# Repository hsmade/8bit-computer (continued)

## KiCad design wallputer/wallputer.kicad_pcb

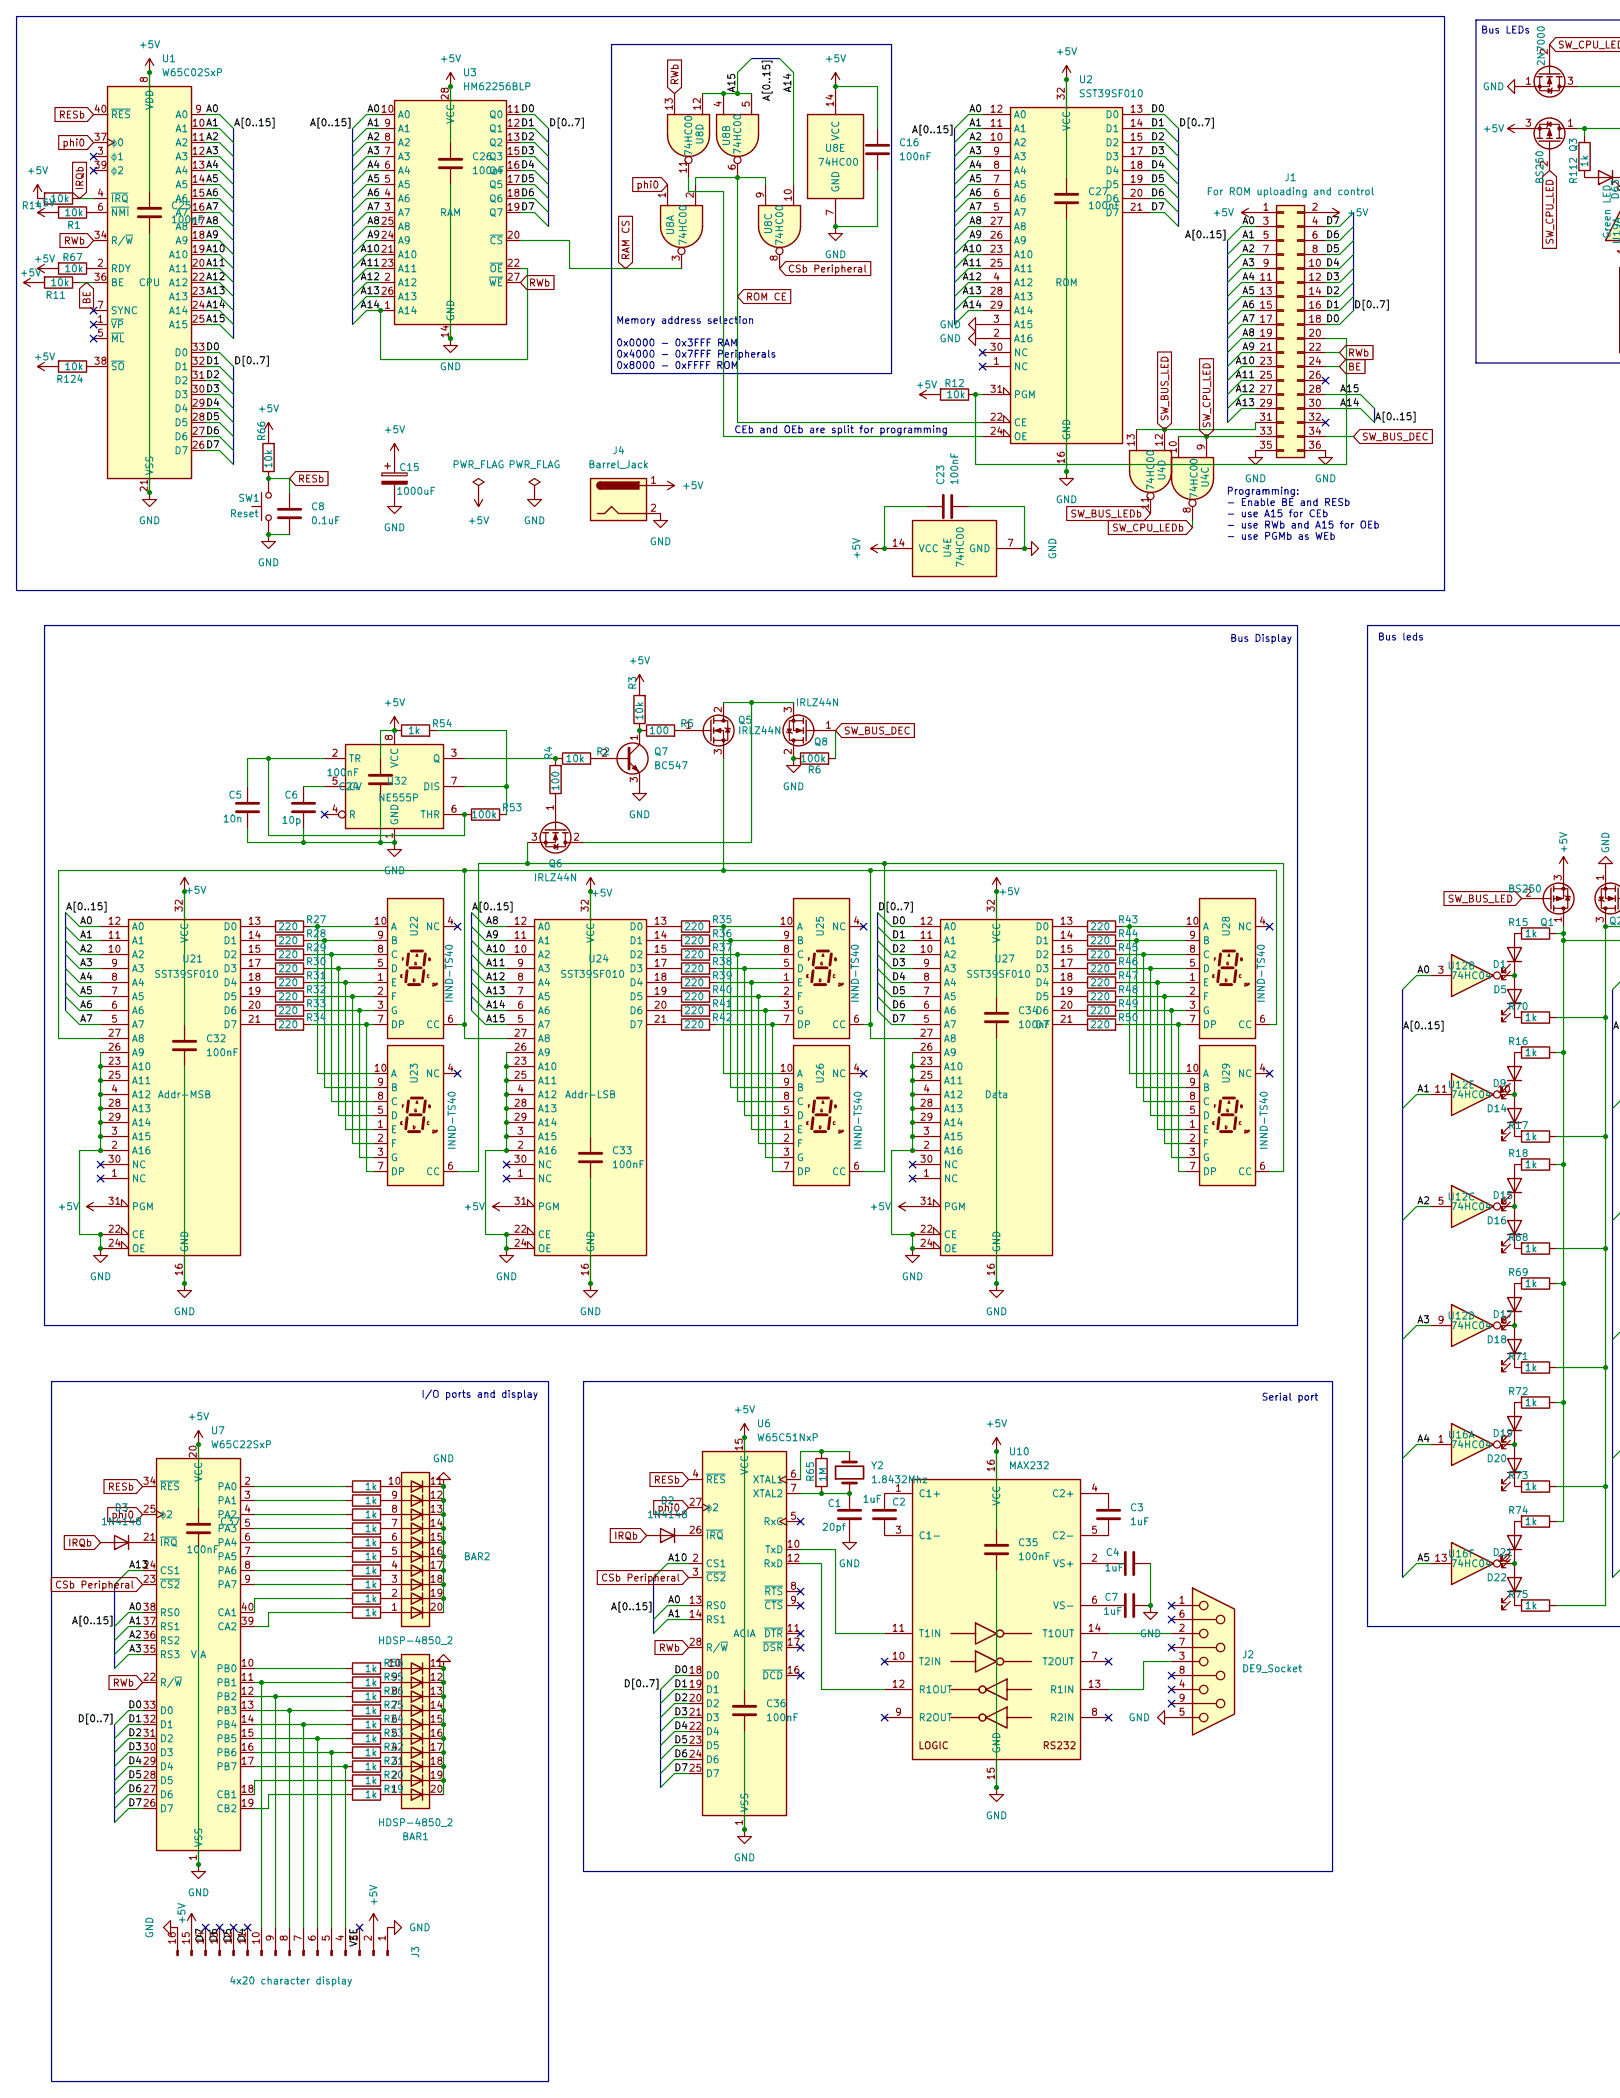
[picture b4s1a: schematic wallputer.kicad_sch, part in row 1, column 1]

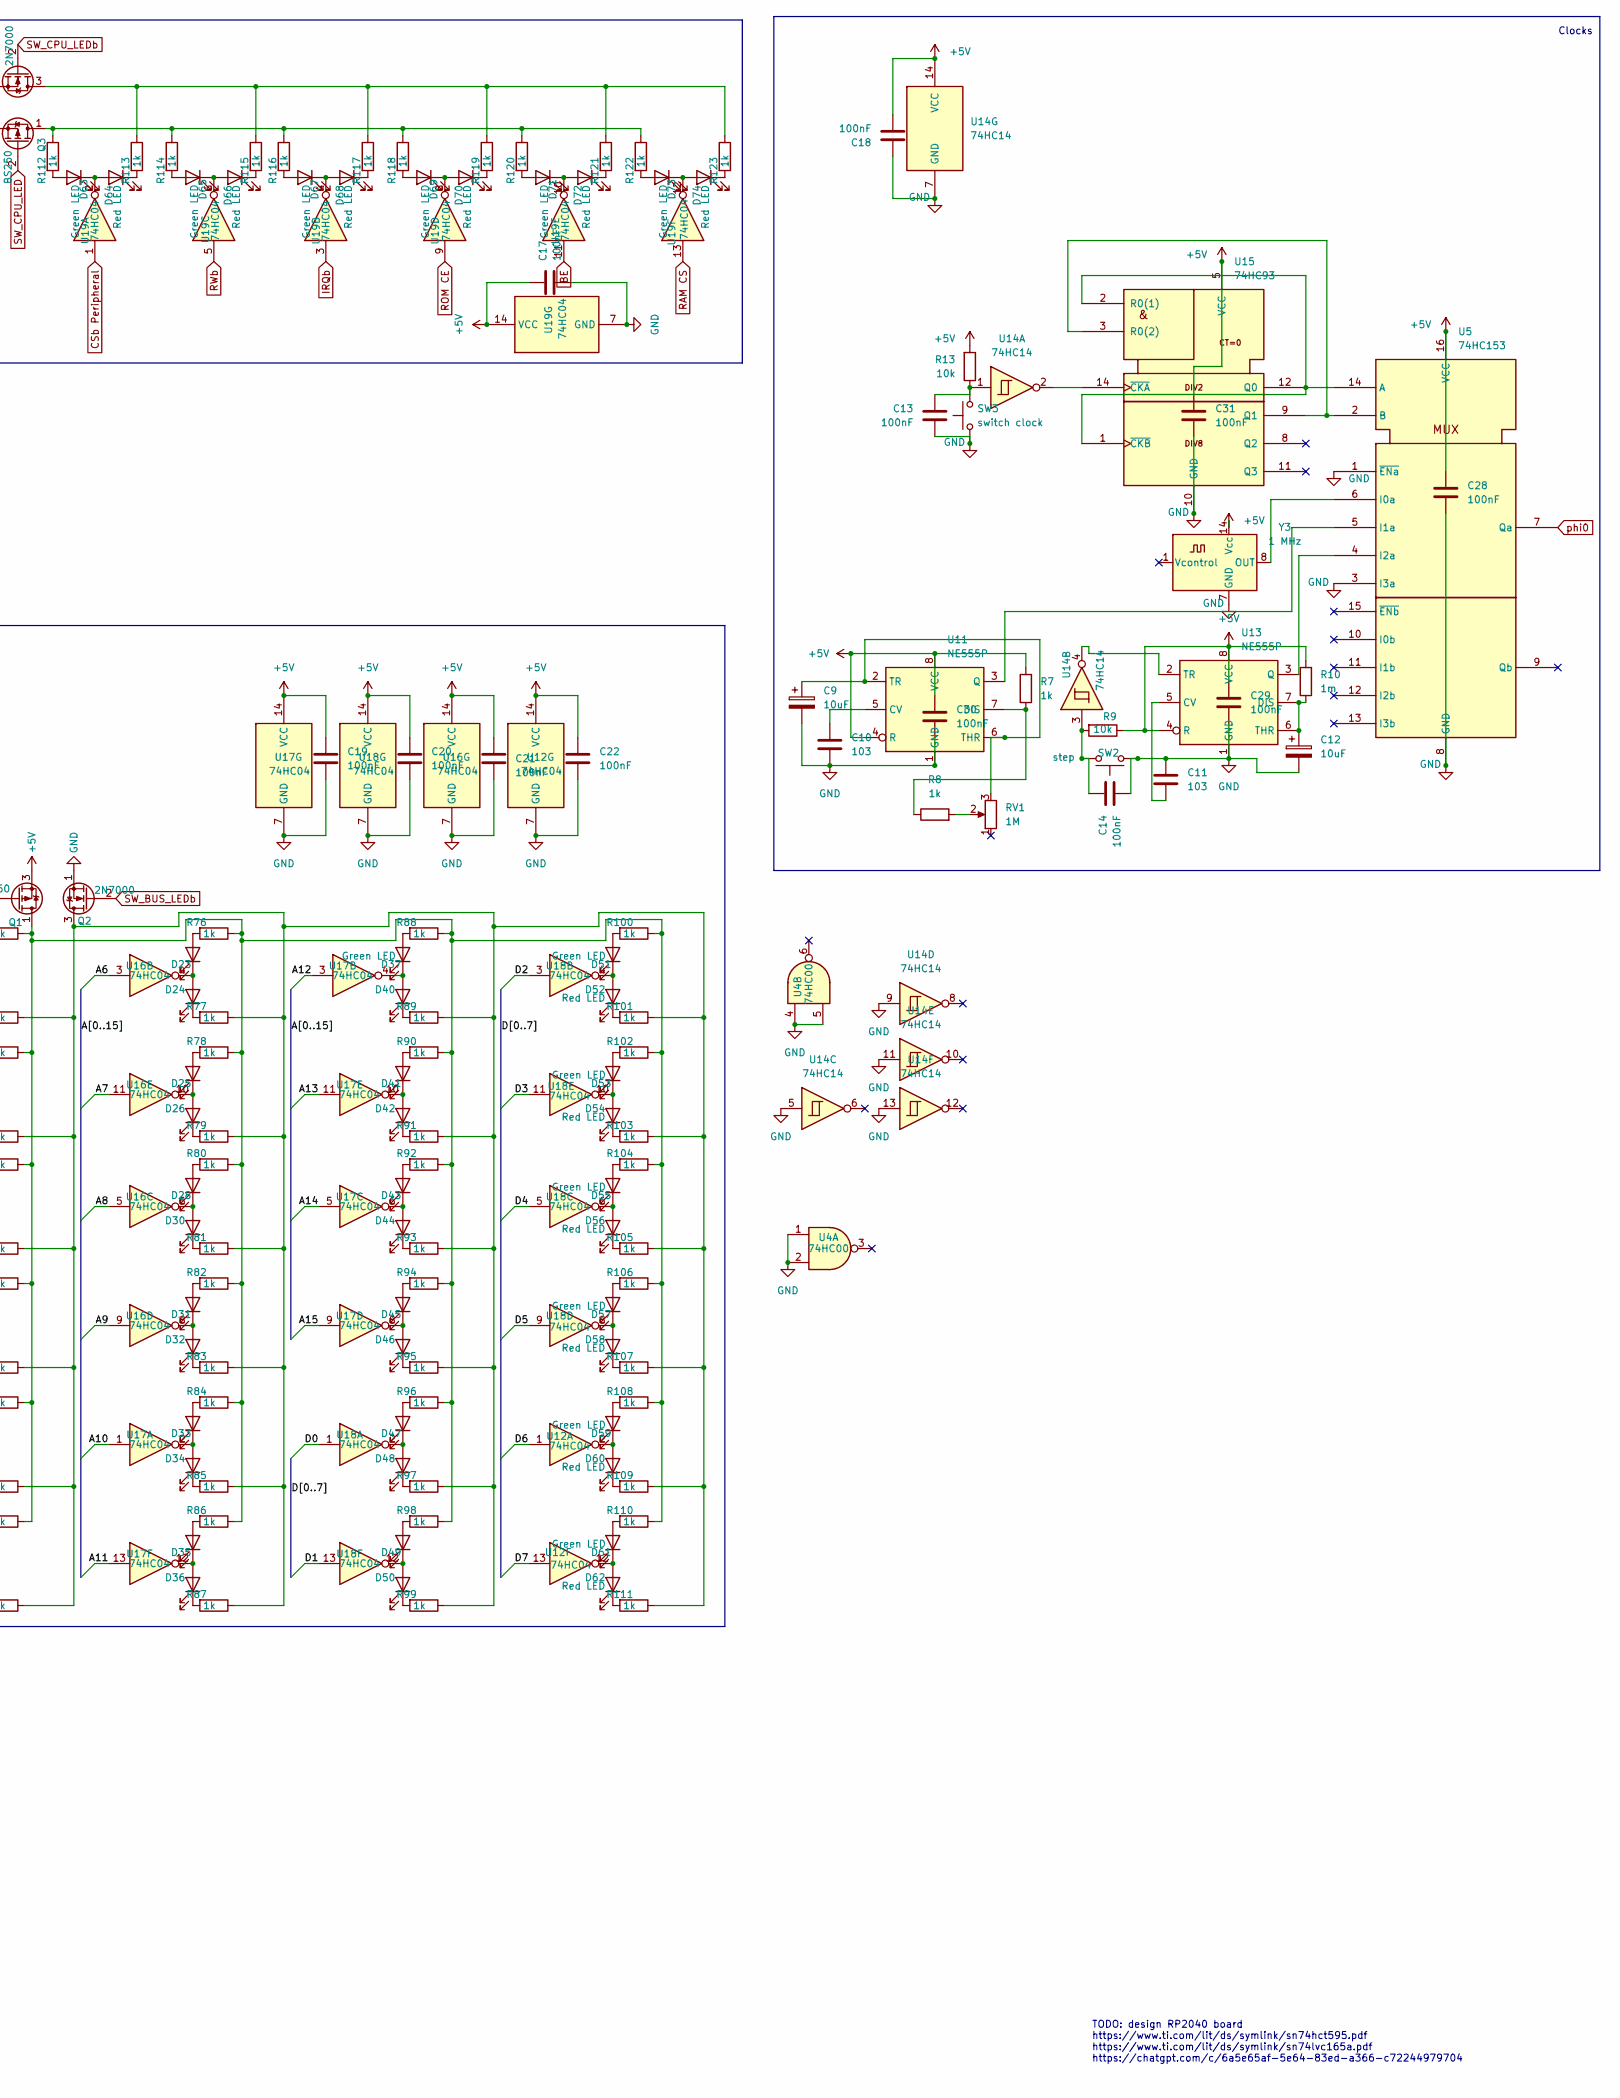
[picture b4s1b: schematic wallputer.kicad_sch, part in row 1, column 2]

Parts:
BAR1, BAR2: HDSP-4850_2; HDSP-4850
C1: 20pf; C_Disc_D5.0mm_W2.5mm_P5.00mm
C2, C3, C4, C7: 1uF; C_Disc_D5.0mm_W2.5mm_P5.00mm
C5: 10n; C_Disc_D5.0mm_W2.5mm_P5.00mm
C6: 10p; C_Disc_D5.0mm_W2.5mm_P5.00mm
C8: 0.1uF; C_Disc_D5.0mm_W2.5mm_P5.00mm
C9, C12: 10uF; CP_Radial_D5.0mm_P2.00mm
C10, C11: 103; C_Disc_D5.0mm_W2.5mm_P5.00mm
C13, C14, C16, C17, C18, C19, C20, C21, C22, C23, C24, C25, C26, C27, C28, C29, C30, C31, C32, C33, C34, C35, C36, C37: 100nF; C_Disc_D5.0mm_W2.5mm_P5.00mm
C15: 1000uF; CP_Axial_L20.0mm_D10.0mm_P26.00mm_Horizontal
D1, D9, D15, D17, D19, D21, D23, D25, D28, D31, D33, D35, D37, D41, D43, D45, D47, D49, D51, D53, D55, D57, D59, D61, D63, D65, D67, D69, D71, D73: Green LED; LED_D3.0mm
D2, D3: 1N4148; D_DO-35_SOD27_P7.62mm_Horizontal
D5, D14, D16, D18, D20, D22, D24, D26, D30, D32, D34, D36, D40, D42, D44, D46, D48, D50, D52, D54, D56, D58, D60, D62, D64, D66, D68, D70, D72, D74: Red LED; LED_D3.0mm
J1: For ROM uploading and control; PinHeader_2x18_P2.54mm_Vertical
J2: DE9_Socket; DSUB-9_Pins_Horizontal_P2.77x2.84mm_EdgePinOffset4.94mm_Hou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
J3: 4x20 character display; PinHeader_1x16_P2.54mm_Vertical
J4: Barrel_Jack; BarrelJack_CUI_PJ-063AH_Horizontal
Q1, Q3: BS250; TO-92_Inline
Q2, Q4: 2N7000; TO-92_Inline
Q5, Q6, Q8: IRLZ44N; TO-220-3_Vertical
Q7: BC547; TO-92_Inline
R1, R2, R3, R9, R11, R12, R13, R14, R66, R67, R124: 10k; R_Axial_DIN0204_L3.6mm_D1.6mm_P2.54mm_Vertical
R4, R5: 100; R_Axial_DIN0204_L3.6mm_D1.6mm_P2.54mm_Vertical
R6, R53: 100k; R_Axial_DIN0204_L3.6mm_D1.6mm_P2.54mm_Vertical
R7, R8, R15, R16, R17, R18, R19, R20, R21, R22, R23, R24, R25, R26, R51, R52, R54, R55, R56, R57, R58, R59, R60, R61, R62, R63, R64, R68, R69, R70, R71, R72, R73, R74, R75, R76, R77, R78, R79, R80, R81, R82, R83, R84, R85, R86, R87, R88, R89, R90, R91, R92, R93, R94, R95, R96, R97, R98, R99, R100, R101, R102, R103, R104, R105, R106, R107, R108, R109, R110, R111, R112, R113, R114, R115, R116, R117, R118, R119, R120, R121, R122, R123: 1k; R_Axial_DIN0204_L3.6mm_D1.6mm_P2.54mm_Vertical
R10: 1m; R_Axial_DIN0204_L3.6mm_D1.6mm_P2.54mm_Vertical
R27, R28, R29, R30, R31, R32, R33, R34, R35, R36, R37, R38, R39, R40, R41, R42, R43, R44, R45, R46, R47, R48, R49, R50: 220; R_Axial_DIN0204_L3.6mm_D1.6mm_P2.54mm_Vertical
R65: 1M; R_Axial_DIN0204_L3.6mm_D1.6mm_P2.54mm_Vertical
RV1: 1M; Potentiometer_Alpha_RD901F-40-00D_Single_Vertical
SW1: Reset; SW_PUSH_6mm_H4.3mm
SW2: step; SW_PUSH_6mm_H4.3mm
SW3: switch clock; SW_PUSH_6mm_H4.3mm
U1: W65C02SxP; DIP-40_W15.24mm_Socket
U2, U21, U24, U27: SST39SF010; DIP-32_W15.24mm_Socket
U3: HM62256BLP; DIP-28_W7.62mm_Socket
U4, U8: 74HC00; DIP-14_W7.62mm_Socket
U5: 74HC153; DIP-16_W7.62mm_Socket
U6: W65C51NxP; DIP-28_W15.24mm
U7: W65C22SxP; DIP-40_W15.24mm
U10: MAX232; DIP-16_W7.62mm_Socket
U11, U13, U32: NE555P; DIP-8_W7.62mm
U12, U16, U17, U18, U19: 74HC04; DIP-14_W7.62mm_Socket
U14: 74HC14; DIP-14_W7.62mm_Socket
U15: 74HC93; DIP-14_W7.62mm_Socket
U22, U23, U25, U26, U28, U29: INND-TS40
Y2: 1.8432Mhz; Crystal_HC18-U_Vertical
Y3: 1 MHz; Oscillator_DIP-14

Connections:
+5V: C15.1, C16.1, C17.1, C18.2, C19.1, C20.1, C21.1, C22.1, C23.1, C24.2, C25.1, C26.1, C27.1, C28.1, C29.1, C30.1, C31.1, C32.1, C33.1, C34.1, C35.1, C36.1, C37.1, J1.1, J1.2, J3.2, J3.15, J4.1, Q1.3 (S), Q3.3 (S), R1.2, R3.2, R7.2, R9.1, R10.2, R11.2, R12.2, R13.2, R14.2, R54.1, R66.2, R67.2, R124.2, U1.8 (VDD), U2.32 (VCC), U3.28 (VCC), U4.14 (VCC), U5.16 (VCC), U6.15 (VCC), U7.20 (VCC), U8.14 (VCC), U10.16 (VCC), U11.4 (R), U11.8 (VCC), U12.14 (VCC), U13.4 (R), U13.8 (VCC), U14.14 (VCC), U15.5 (VCC), U16.14 (VCC), U17.14 (VCC), U18.14 (VCC), U19.14 (VCC), U21.31 (PGM), U21.32 (VCC), U24.31 (PGM), U24.32 (VCC), U27.31 (PGM), U27.32 (VCC), U32.8 (VCC), Y3.14 (Vcc)
/A0: J1.3, U1.9 (A0), U2.12 (A0), U3.10 (A0), U6.13 (RS0), U7.38 (RS0), U12.3, U21.12 (A0)
/A1: J1.5, U1.10 (A1), U2.11 (A1), U3.9 (A1), U6.14 (RS1), U7.37 (RS1), U12.11, U21.11 (A1)
/A2: J1.7, U1.11 (A2), U2.10 (A2), U3.8 (A2), U7.36 (RS2), U12.5, U21.10 (A2)
/A3: J1.9, U1.12 (A3), U2.9 (A3), U3.7 (A3), U7.35 (RS3), U12.9, U21.9 (A3)
/A4: J1.11, U1.13 (A4), U2.8 (A4), U3.6 (A4), U16.1, U21.8 (A4)
/A5: J1.13, U1.14 (A5), U2.7 (A5), U3.5 (A5), U16.13, U21.7 (A5)
/A6: J1.15, U1.15 (A6), U2.6 (A6), U3.4 (A6), U16.3, U21.6 (A6)
/A7: J1.17, U1.16 (A7), U2.5 (A7), U3.3 (A7), U16.11, U21.5 (A7)
/A8: J1.19, U1.17 (A8), U2.27 (A8), U3.25 (A8), U16.5, U24.12 (A0)
/A9: J1.21, U1.18 (A9), U2.26 (A9), U3.24 (A9), U16.9, U24.11 (A1)
/A10: J1.23, U1.19 (A10), U2.23 (A10), U3.21 (A10), U6.2 (CS1), U17.1, U24.10 (A2)
/A11: J1.25, U1.20 (A11), U2.25 (A11), U3.23 (A11), U17.13, U24.9 (A3)
/A12: J1.27, U1.22 (A12), U2.4 (A12), U3.2 (A12), U17.3, U24.8 (A4)
/A13: J1.29, U1.23 (A13), U2.28 (A13), U3.26 (A13), U7.24 (CS1), U17.11, U24.7 (A5)
/A14: J1.30, U1.24 (A14), U2.29 (A14), U3.1 (A14), U3.22 (~OE), U8.10, U17.5, U24.6 (A6)
/A15: J1.28, U1.25 (A15), U8.4, U8.5, U8.12, U17.9, U24.5 (A7)
/D0: J1.18, U1.33 (D0), U2.13 (D0), U3.11 (Q0), U6.18 (D0), U7.33 (D0), U18.1, U27.12 (A0)
/D1: J1.16, U1.32 (D1), U2.14 (D1), U3.12 (Q1), U6.19 (D1), U7.32 (D1), U18.13, U27.11 (A1)
/D2: J1.14, U1.31 (D2), U2.15 (D2), U3.13 (Q2), U6.20 (D2), U7.31 (D2), U18.3, U27.10 (A2)
/D3: J1.12, U1.30 (D3), U2.17 (D3), U3.15 (Q3), U6.21 (D3), U7.30 (D3), U18.11, U27.9 (A3)
/D4: J1.10, J3.11, U1.29 (D4), U2.18 (D4), U3.16 (Q4), U6.22 (D4), U7.29 (D4), U18.5, U27.8 (A4)
/D5: J1.8, J3.12, U1.28 (D5), U2.19 (D5), U3.17 (Q5), U6.23 (D5), U7.28 (D5), U18.9, U27.7 (A5)
/D6: J1.6, J3.13, U1.27 (D6), U2.20 (D6), U3.18 (Q6), U6.24 (D6), U7.27 (D6), U12.1, U27.6 (A6)
/D7: J1.4, J3.14, U1.26 (D7), U2.21 (D7), U3.19 (Q7), U6.25 (D7), U7.26 (D7), U12.13, U27.5 (A7)
/VEE: J3.3
BE: J1.24, R11.1, U1.36 (BE), U19.11
CSb Peripheral: U6.3 (~CS2), U7.23 (~CS2), U8.8, U19.1
GND: BAR1.11 (K), BAR1.12 (K), BAR1.13 (K), BAR1.14 (K), BAR1.15 (K), BAR1.16 (K), BAR1.17 (K), BAR1.18 (K), BAR1.19 (K), BAR1.20 (K), BAR2.11 (K), BAR2.12 (K), BAR2.13 (K), BAR2.14 (K), BAR2.15 (K), BAR2.16 (K), BAR2.17 (K), BAR2.18 (K), BAR2.19 (K), BAR2.20 (K), C1.2, C4.2, C5.2, C6.2, C7.2, C8.2, C9.2, C10.2, C11.1, C12.2, C13.2, C14.2, C15.2, C16.2, C17.2, C18.1, C19.2, C20.2, C21.2, C22.2, C23.2, C24.1, C25.2, C26.2, C27.2, C28.2, C29.2, C30.2, C31.2, C32.2, C33.2, C34.2, C35.2, C36.2, C37.2, J1.35, J1.36, J2.5, J3.1, J3.16, J4.2, Q2.1 (S), Q4.1 (S), Q7.3 (E), Q8.2 (D), R6.1, SW1.1, SW2.1, SW3.1, U1.21 (VSS), U2.2 (A16), U2.3 (A15), U2.16 (GND), U3.14 (GND), U4.1, U4.2, U4.4, U4.5, U4.7 (GND), U5.1 (~ENa), U5.3 (I3a), U5.8 (GND), U6.1 (VSS), U7.1 (VSS), U8.7 (GND), U10.15 (GND), U11.1 (GND), U12.7 (GND), U13.1 (GND), U14.5, U14.7 (GND), U14.9, U14.11, U14.13, U15.10 (GND), U16.7 (GND), U17.7 (GND), U18.7 (GND), U19.7 (GND), U21.2 (A16), U21.3 (A15), U21.4 (A12), U21.16 (GND), U21.22 (CE), U21.23 (A10), U21.24 (OE), U21.25 (A11), U21.26 (A9), U21.28 (A13), U21.29 (A14), U24.2 (A16), U24.3 (A15), U24.4 (A12), U24.16 (GND), U24.22 (CE), U24.23 (A10), U24.24 (OE), U24.25 (A11), U24.26 (A9), U24.28 (A13), U24.29 (A14), U27.2 (A16), U27.3 (A15), U27.4 (A12), U27.16 (GND), U27.22 (CE), U27.23 (A10), U27.24 (OE), U27.25 (A11), U27.26 (A9), U27.28 (A13), U27.29 (A14), U32.1 (GND), Y3.7 (GND)
IRQb: D2.2 (A), D3.2 (A), R14.1, U1.4 (~IRQ), U19.3
unnamed: BAR1.1 (A), R19.2
unnamed: BAR1.2 (A), R20.2
unnamed: BAR1.3 (A), R21.2
unnamed: BAR1.4 (A), R22.2
unnamed: BAR1.5 (A), R23.2
unnamed: BAR1.6 (A), R24.2
unnamed: BAR1.7 (A), R25.2
unnamed: BAR1.8 (A), R26.2
unnamed: BAR1.9 (A), R55.2
unnamed: BAR1.10 (A), R56.2
unnamed: BAR2.1 (A), R59.2
unnamed: BAR2.2 (A), R60.2
unnamed: BAR2.3 (A), R61.2
unnamed: BAR2.4 (A), R62.2
unnamed: BAR2.5 (A), R63.2
unnamed: BAR2.6 (A), R64.2
unnamed: BAR2.7 (A), R58.2
unnamed: BAR2.8 (A), R57.2
unnamed: BAR2.9 (A), R52.2
unnamed: BAR2.10 (A), R51.2
unnamed: C13.1, R13.1, SW3.2, U14.1
unnamed: C14.1, R9.2, SW2.2, U14.3
unnamed: D1.2 (A), R15.2
unnamed: D1.1 (K), D5.2 (A), U12.4
unnamed: D2.1 (K), U6.26 (~IRQ)
unnamed: D3.1 (K), U7.21 (~IRQ)
unnamed: D5.1 (K), R70.2
unnamed: D9.2 (A), R16.2
unnamed: D9.1 (K), D14.2 (A), U12.10
unnamed: D14.1 (K), R17.2
unnamed: D15.2 (A), R18.2
unnamed: D15.1 (K), D16.2 (A), U12.6
unnamed: D16.1 (K), R68.2
unnamed: D17.2 (A), R69.2
unnamed: D17.1 (K), D18.2 (A), U12.8
unnamed: D18.1 (K), R71.2
unnamed: D19.2 (A), R72.2
unnamed: D19.1 (K), D20.2 (A), U16.2
unnamed: D20.1 (K), R73.2
unnamed: D21.2 (A), R74.2
unnamed: D21.1 (K), D22.2 (A), U16.12
unnamed: D22.1 (K), R75.2
unnamed: D23.2 (A), R76.2
unnamed: D23.1 (K), D24.2 (A), U16.4
unnamed: D24.1 (K), R77.2
unnamed: D25.2 (A), R78.2
unnamed: D25.1 (K), D26.2 (A), U16.10
unnamed: D26.1 (K), R79.2
unnamed: D28.2 (A), R80.2
unnamed: D28.1 (K), D30.2 (A), U16.6
unnamed: D30.1 (K), R81.2
unnamed: D31.2 (A), R82.2
unnamed: D31.1 (K), D32.2 (A), U16.8
unnamed: D32.1 (K), R83.2
unnamed: D33.2 (A), R84.2
unnamed: D33.1 (K), D34.2 (A), U17.2
unnamed: D34.1 (K), R85.2
unnamed: D35.2 (A), R86.2
unnamed: D35.1 (K), D36.2 (A), U17.12
unnamed: D36.1 (K), R87.2
unnamed: D37.2 (A), R88.2
unnamed: D37.1 (K), D40.2 (A), U17.4
unnamed: D40.1 (K), R89.2
unnamed: D41.2 (A), R90.2
unnamed: D41.1 (K), D42.2 (A), U17.10
unnamed: D42.1 (K), R91.2
unnamed: D43.2 (A), R92.2
unnamed: D43.1 (K), D44.2 (A), U17.6
unnamed: D44.1 (K), R93.2
unnamed: D45.2 (A), R94.2
unnamed: D45.1 (K), D46.2 (A), U17.8
unnamed: D46.1 (K), R95.2
unnamed: D47.2 (A), R96.2
unnamed: D47.1 (K), D48.2 (A), U18.2
unnamed: D48.1 (K), R97.2
unnamed: D49.2 (A), R98.2
unnamed: D49.1 (K), D50.2 (A), U18.12
unnamed: D50.1 (K), R99.2
unnamed: D51.2 (A), R100.2
unnamed: D51.1 (K), D52.2 (A), U18.4
unnamed: D52.1 (K), R101.2
unnamed: D53.2 (A), R102.2
unnamed: D53.1 (K), D54.2 (A), U18.10
unnamed: D54.1 (K), R103.2
unnamed: D55.2 (A), R104.2
unnamed: D55.1 (K), D56.2 (A), U18.6
unnamed: D56.1 (K), R105.2
unnamed: D57.2 (A), R106.2
unnamed: D57.1 (K), D58.2 (A), U18.8
unnamed: D58.1 (K), R107.2
unnamed: D59.2 (A), R108.2
unnamed: D59.1 (K), D60.2 (A), U12.2
unnamed: D60.1 (K), R109.2
unnamed: D61.2 (A), R110.2
unnamed: D61.1 (K), D62.2 (A), U12.12
unnamed: D62.1 (K), R111.2
unnamed: D63.2 (A), R112.2
unnamed: D63.1 (K), D64.2 (A), U19.2
unnamed: D64.1 (K), R113.2
unnamed: D65.2 (A), R114.2
unnamed: D65.1 (K), D66.2 (A), U19.6
unnamed: D66.1 (K), R115.2
unnamed: D67.2 (A), R116.2
unnamed: D67.1 (K), D68.2 (A), U19.4
unnamed: D68.1 (K), R117.2
unnamed: D69.2 (A), R118.2
unnamed: D69.1 (K), D70.2 (A), U19.8
unnamed: D70.1 (K), R119.2
unnamed: D71.2 (A), R120.2
unnamed: D71.1 (K), D72.2 (A), U19.10
unnamed: D72.1 (K), R121.2
unnamed: D73.2 (A), R122.2
unnamed: D73.1 (K), D74.2 (A), U19.12
unnamed: D74.1 (K), R123.2
unnamed: J1.20, R12.1, U2.31 (PGM)
unnamed: J3.4, R21.1, U7.17 (PB7)
unnamed: J3.5, R22.1, U7.16 (PB6)
unnamed: J3.6, R23.1, U7.15 (PB5)
unnamed: J3.7, R24.1, U7.14 (PB4)
unnamed: J3.8, R25.1, U7.13 (PB3)
unnamed: J3.9, R26.1, U7.12 (PB2)
unnamed: J3.10, R55.1, U7.11 (PB1)
unnamed: Q1.1 (D), R15.1, R16.1, R18.1, R69.1, R72.1, R74.1, R76.1, R78.1, R80.1, R82.1, R84.1, R86.1, R88.1, R90.1, R92.1, R94.1, R96.1, R98.1, R100.1, R102.1, R104.1, R106.1, R108.1, R110.1
unnamed: Q2.3 (D), R17.1, R68.1, R70.1, R71.1, R73.1, R75.1, R77.1, R79.1, R81.1, R83.1, R85.1, R87.1, R89.1, R91.1, R93.1, R95.1, R97.1, R99.1, R101.1, R103.1, R105.1, R107.1, R109.1, R111.1
unnamed: Q3.1 (D), R112.1, R114.1, R116.1, R118.1, R120.1, R122.1
unnamed: Q4.3 (D), R113.1, R115.1, R117.1, R119.1, R121.1, R123.1
unnamed: Q5.2 (D), Q6.2 (D), Q8.3 (S)
unnamed: Q5.1 (G), R5.2
unnamed: Q5.3 (S), U21.27 (A8), U22.6 (CC), U24.27 (A8), U25.6 (CC), U27.27 (A8), U28.6 (CC)
unnamed: Q6.1 (G), R4.1
unnamed: Q6.3 (S), U23.6 (CC), U26.6 (CC), U29.6 (CC)
unnamed: Q7.2 (B), R2.2
unnamed: Q7.1 (C), R3.1, R5.1
unnamed: R8.2, RV1.2
unnamed: R67.1, U1.2 (RDY)
unnamed: R1.1, U1.6 (~NMI)
unnamed: R124.1, U1.38 (~SO)
unnamed: U2.24 (OE), U8.11
unnamed: U5.6 (I0a), Y3.8 (OUT)
unnamed: R65.1, U6.6 (XTAL1), Y2.2
unnamed: C1.1, R65.2, U6.7 (XTAL2), Y2.1
unnamed: R60.1, U7.40 (CA1)
unnamed: R59.1, U7.39 (CA2)
unnamed: R20.1, U7.18 (CB1)
unnamed: R19.1, U7.19 (CB2)
unnamed: R51.1, U7.2 (PA0)
unnamed: R52.1, U7.3 (PA1)
unnamed: R57.1, U7.4 (PA2)
unnamed: R58.1, U7.5 (PA3)
unnamed: R64.1, U7.6 (PA4)
unnamed: R63.1, U7.7 (PA5)
unnamed: R62.1, U7.8 (PA6)
unnamed: R61.1, U7.9 (PA7)
unnamed: R56.1, U7.10 (PB0)
unnamed: C2.1, U10.1 (C1+)
unnamed: C2.2, U10.3 (C1-)
unnamed: C3.1, U10.4 (C2+)
unnamed: C3.2, U10.5 (C2-)
unnamed: J2.3, U10.13 (R1IN)
unnamed: U6.12 (RxD), U10.12 (R1OUT)
unnamed: U6.10 (TxD), U10.11 (T1IN)
unnamed: J2.2, U10.14 (T1OUT)
unnamed: C4.1, U10.2 (VS+)
unnamed: C7.1, U10.6 (VS-)
unnamed: C10.1, U11.5 (CV)
unnamed: R7.1, R8.1, U11.7 (DIS)
unnamed: U5.5 (I1a), U11.3 (Q)
unnamed: C9.1, RV1.3, U11.2 (TR), U11.6 (THR)
unnamed: C11.2, U13.5 (CV)
unnamed: C12.1, R10.1, U13.6 (THR), U13.7 (DIS)
unnamed: U5.4 (I2a), U13.3 (Q)
unnamed: U13.2 (TR), U14.4
unnamed: U5.14 (A), U15.1 (~CKB), U15.2 (R0(1)), U15.12 (Q0)
unnamed: U5.2 (B), U15.3 (R0(2)), U15.9 (Q1)
unnamed: U14.2, U15.14 (~CKA)
unnamed: R27.1, U21.13 (D0)
unnamed: R28.1, U21.14 (D1)
unnamed: R29.1, U21.15 (D2)
unnamed: R30.1, U21.17 (D3)
unnamed: R31.1, U21.18 (D4)
unnamed: R32.1, U21.19 (D5)
unnamed: R33.1, U21.20 (D6)
unnamed: R34.1, U21.21 (D7)
unnamed: R27.2, U22.10 (A), U23.10 (A)
unnamed: R28.2, U22.9 (B), U23.9 (B)
unnamed: R29.2, U22.8 (C), U23.8 (C)
unnamed: R30.2, U22.5 (D), U23.5 (D)
unnamed: R34.2, U22.7 (DP), U23.7 (DP)
unnamed: R31.2, U22.1 (E), U23.1 (E)
unnamed: R32.2, U22.2 (F), U23.2 (F)
unnamed: R33.2, U22.3 (G), U23.3 (G)
unnamed: R35.1, U24.13 (D0)
unnamed: R36.1, U24.14 (D1)
unnamed: R37.1, U24.15 (D2)
unnamed: R38.1, U24.17 (D3)
unnamed: R39.1, U24.18 (D4)
unnamed: R40.1, U24.19 (D5)
unnamed: R41.1, U24.20 (D6)
unnamed: R42.1, U24.21 (D7)
unnamed: R35.2, U25.10 (A), U26.10 (A)
unnamed: R36.2, U25.9 (B), U26.9 (B)
unnamed: R37.2, U25.8 (C), U26.8 (C)
unnamed: R38.2, U25.5 (D), U26.5 (D)
unnamed: R42.2, U25.7 (DP), U26.7 (DP)
unnamed: R39.2, U25.1 (E), U26.1 (E)
unnamed: R40.2, U25.2 (F), U26.2 (F)
unnamed: R41.2, U25.3 (G), U26.3 (G)
unnamed: R43.1, U27.13 (D0)
unnamed: R44.1, U27.14 (D1)
unnamed: R45.1, U27.15 (D2)
unnamed: R46.1, U27.17 (D3)
unnamed: R47.1, U27.18 (D4)
unnamed: R48.1, U27.19 (D5)
unnamed: R49.1, U27.20 (D6)
unnamed: R50.1, U27.21 (D7)
unnamed: R43.2, U28.10 (A), U29.10 (A)
unnamed: R44.2, U28.9 (B), U29.9 (B)
unnamed: R45.2, U28.8 (C), U29.8 (C)
unnamed: R46.2, U28.5 (D), U29.5 (D)
unnamed: R50.2, U28.7 (DP), U29.7 (DP)
unnamed: R47.2, U28.1 (E), U29.1 (E)
unnamed: R48.2, U28.2 (F), U29.2 (F)
unnamed: R49.2, U28.3 (G), U29.3 (G)
unnamed: C6.1, U32.5 (CV)
unnamed: R53.2, R54.2, U32.7 (DIS)
unnamed: R2.1, R4.2, U32.3 (Q)
unnamed: C5.1, R53.1, U32.2 (TR), U32.6 (THR)
RAM CS: U3.20 (~CS), U8.3, U19.13
RESb: C8.1, R66.1, SW1.2, U1.40 (~RES), U6.4 (~RES), U7.34 (~RES)
ROM CE: U2.22 (CE), U8.2, U8.6, U8.9, U19.9
RWb: J1.22, U1.34 (R/~W), U3.27 (~WE), U6.28 (R/~W), U7.22 (R/~W), U8.13, U19.5
SW_BUS_DEC: J1.34, Q8.1 (G), R6.2
SW_BUS_LED: J1.31, Q1.2 (G), U4.12, U4.13
SW_BUS_LEDb: Q2.2 (G), U4.11
SW_CPU_LED: J1.33, Q3.2 (G), U4.9, U4.10
SW_CPU_LEDb: Q4.2 (G), U4.8
phi0: U1.37 (ϕ0), U5.7 (Qa), U6.27 (ϕ2), U7.25 (ϕ2), U8.1

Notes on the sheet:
Memory address selection 0x0000 - 0x3FFF RAM 0x4000 - 0x7FFF Peripherals 0x8000 - 0xFFFF ROM
Bus LEDs
Clocks
TODO: design RP2040 board https://www.ti.com/lit/ds/symlink/sn74hct595.pdf https://www.ti.com/lit/ds/symlink/sn74lvc165a.pdf https://chatgpt.com/c/6a5e65af-5e64-83ed-a366-c72244979704
Bus Display
I/O ports and display
Bus leds
Serial port
Programming: - Enable BE and RESb - use A15 for CEb - use RWb and A15 for OEb - use PGMb as WEb
CEb and OEb are split for programming

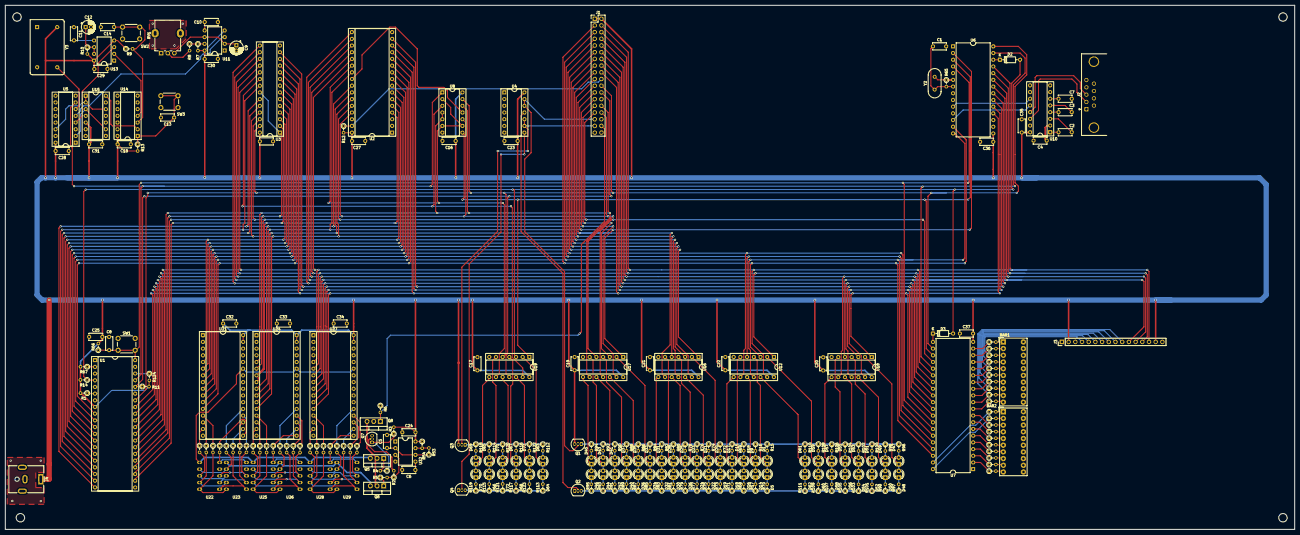
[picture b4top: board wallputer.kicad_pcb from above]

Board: 2 copper layers, 488.9 x 198.8 mm, 270 parts (0 on the bottom side), 266 nets.
